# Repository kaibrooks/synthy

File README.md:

# synthy
PROJECT THEREMIZER

This file describes the THEREMIZER built by Bader Almatouq, Kai Brooks, Andrew Forsman, and Jeff Roman in Fall 
of 2019 for ECE 411 at Portland State University.

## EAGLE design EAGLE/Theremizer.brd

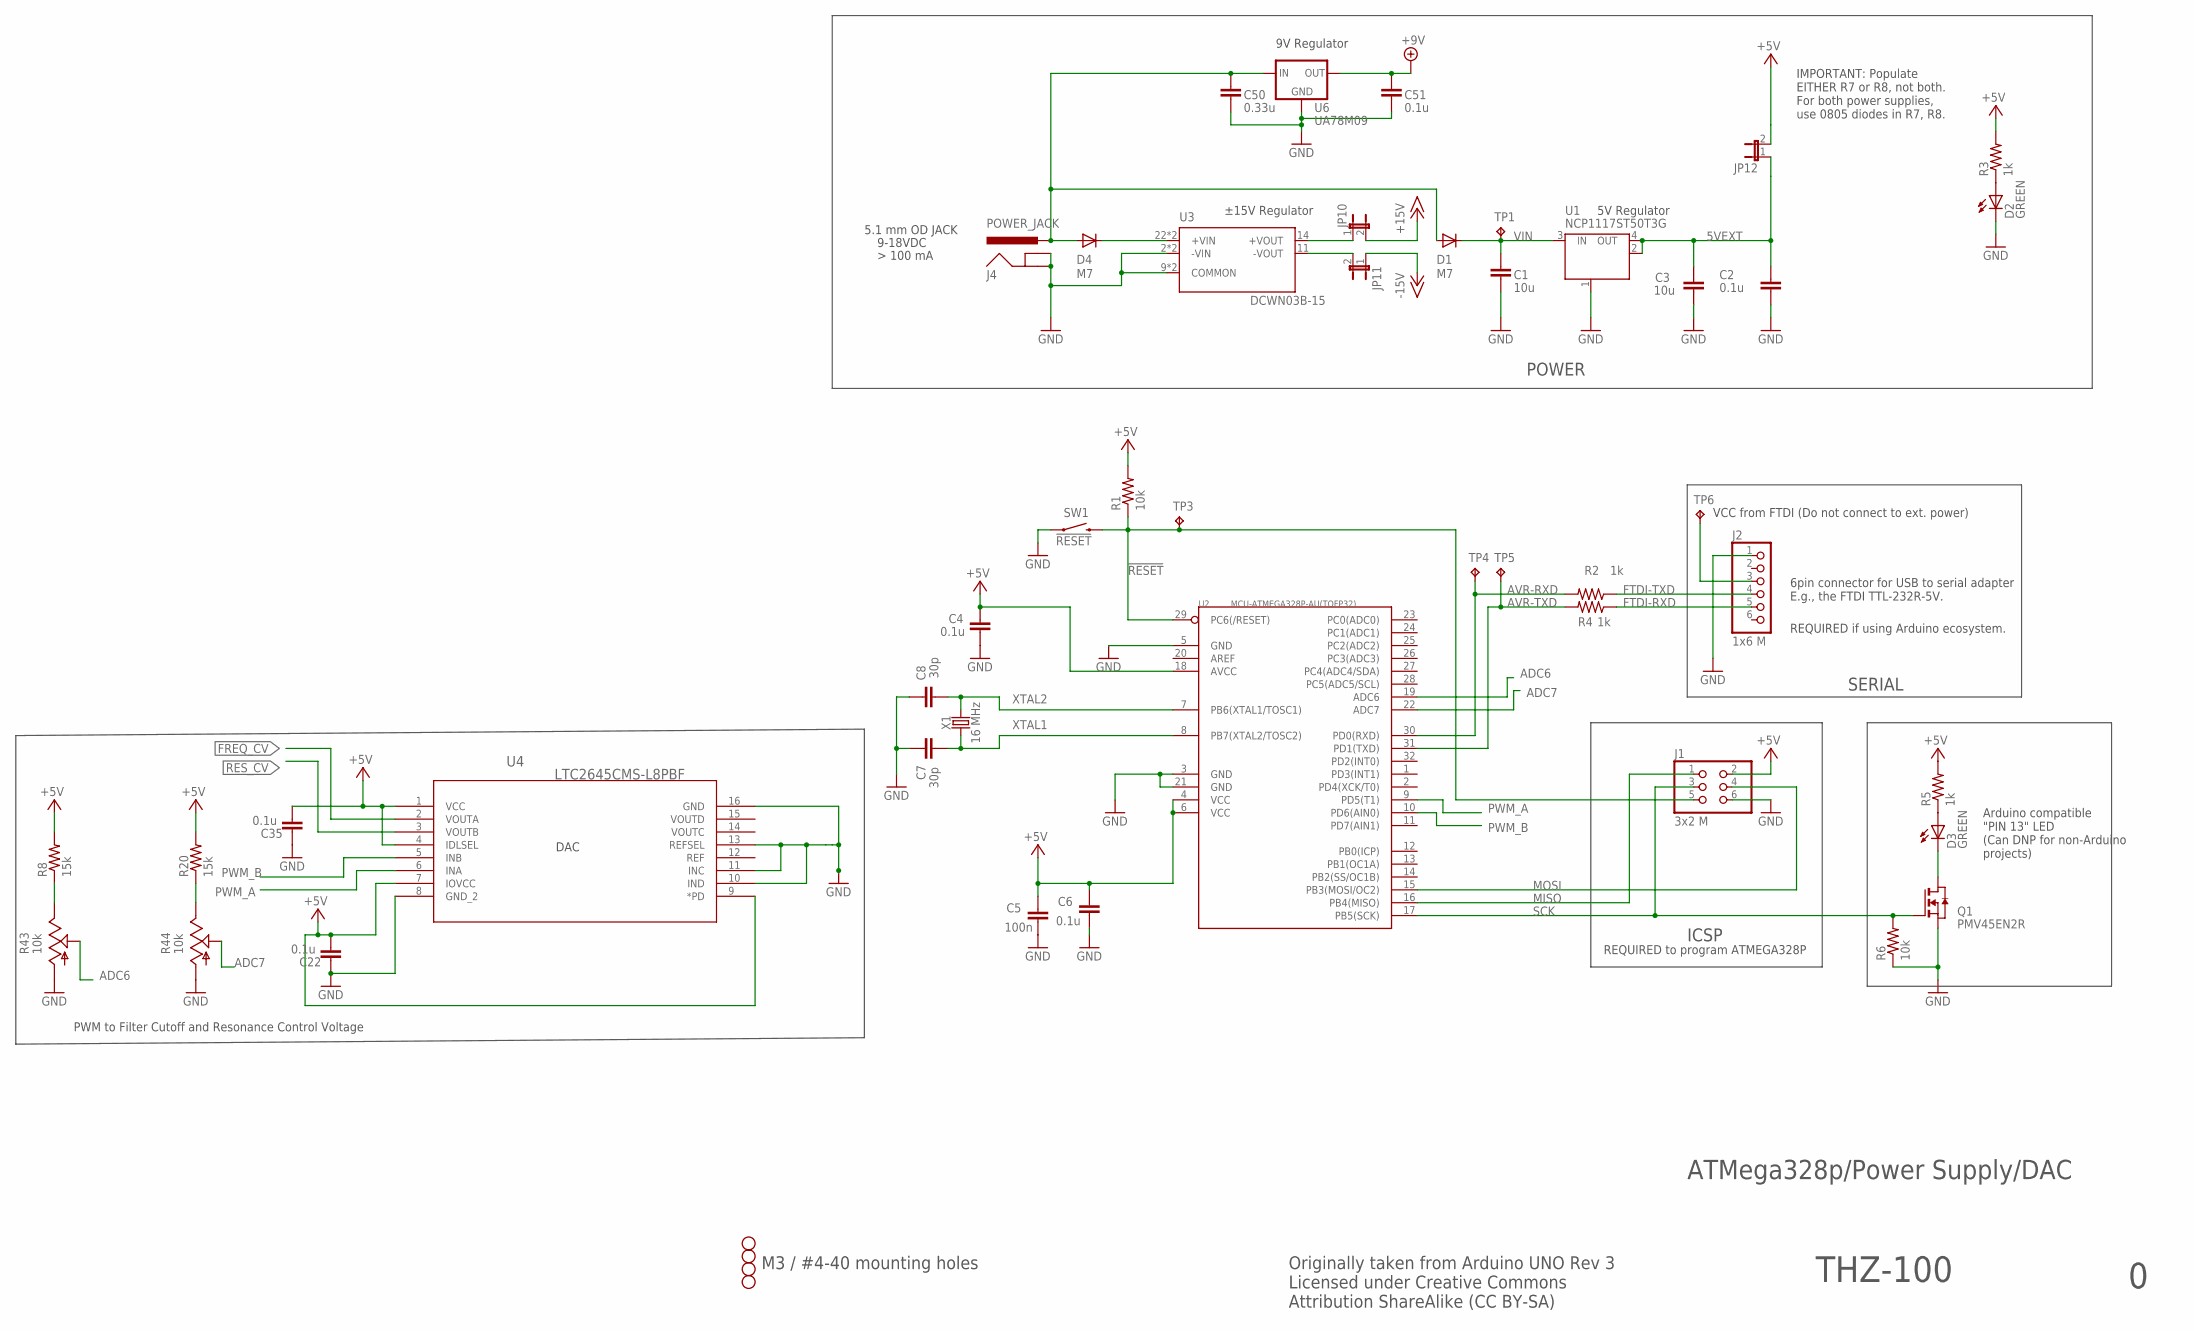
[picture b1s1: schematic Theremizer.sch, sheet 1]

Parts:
C1, C3: 10u; C0805; MPN CL21A106KOQNNNG
C2, C4, C6: 0.1u; C0805; MPN CL21B104KBCNNNC
C5: 100n; C0805; MPN CL21B104KBCNNNC
C7: 30p; C0805; MPN CL21C180JBANNNC
C8: 30p; C0805; MPN CL21C300JBANNNC
C22: 0.1u; C0805K; MPN CL21C300JBANNNC
C35: 0.1u; C0805; MPN CL21C300JBANNNC
C50: 0.33u; C0805; MPN CL21A106KOQNNNG
C51: 0.1u; C0805; MPN CL21A106KOQNNNG
D1, D4: M7; SMB; MPN 10BQ030TR
D2, D3: GREEN; CHIP-LED0805; MPN 150080GS75000
H1, H2, H3, H4: STAND-OFF
J1: 3x2 M; 2X03; MPN M20-9980345
J2: 1x6 M; 1X06; MPN PRPC006SAAN-RC
J4: POWER_JACK; POWER_JACK_PTH; MPN PJ-202A
JP10, JP11, JP12: JP1E; JP1
Q1: PMV45EN2R; SOT-23; MPN PMV45EN2R
R1, R6: 10k; R0805; MPN RC0805FR-0710KL
R2, R3, R4, R5: 1k; R0805; MPN RC0805FR-071KL
R8, R20: 15k; R0805; MPN RC0805FR-0710KL
R43, R44: 10k; ECP10P
SW1: !RESET; TACTILE_SWITCH_SMD; MPN RS-187R05A2-DS MT RT
TP1, TP3, TP4, TP5, TP6: TPPAD1-13; P1-13
U1: NCP1117ST50T3G; SOT223; MPN NCP1117ST50T3G
U2: MCU-ATMEGA328P-AU(TQFP32); TQFP32-0.8-7X7MM
U3: DCWN03B-15; DIP1549W45P254L3404H940Q24
U4: LTC2645CMS-L8PBF; MSOP-16_MS
U6: UA78M09; DPACK
X1: 16 MHz; HC49UP; MPN ECS-160-18-5PX-TR

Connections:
5VEXT: C2.2, C3.1, JP12.1, U1.2 (OUT), U1.4 (OUT)
!RESET: J1.5, R1.1, SW1.3 (2), TP3.TP, U2.29 (PC6(/RESET))
+5V: C4.2, C5.2, C6.2, C22.1, C35.1, J1.2, JP12.2, R1.2, R3.2, R5.2, R8.2, R20.2, U2.4 (VCC), U2.6 (VCC), U2.18 (AVCC), U4.1 (VCC), U4.4 (IDLSEL), U4.7 (IOVCC), U4.9 (*PD); also elsewhere on the board
+9V: C51.1, U6.3 (OUT); also elsewhere on the board
+15V: JP10.2; also elsewhere on the board
-15V: JP11.1; also elsewhere on the board
ADC6: R43.S, U2.19 (ADC6)
ADC7: R44.S, U2.22 (ADC7)
AVR-RXD: R2.2, TP4.TP, U2.30 (PD0(RXD))
AVR-TXD: R4.2, TP5.TP, U2.31 (PD1(TXD))
FREQ_CV: U4.2 (VOUTA); also elsewhere on the board
FTDI-RXD: J2.5, R4.1
FTDI-TXD: J2.4, R2.1
GND: C1.2, C2.1, C3.2, C4.1, C5.1, C6.1, C7.2, C8.2, C22.2, C35.2, C50.2, C51.2, D2.C, J1.6, J2.1, J4.GND, J4.GNDBREAK, Q1.2 (S), R6.1, R43.A, R44.A, SW1.1, U1.1 (GND/ADJ), U2.3 (GND), U2.5 (GND), U2.21 (GND), U3.2 (-VIN), U3.3 (-VIN), U3.9 (COMMON), U3.16 (COMMON), U4.8 (GND_2), U4.10 (IND), U4.11 (INC), U4.13 (REFSEL), U4.16 (GND), U6.4 (GND); also elsewhere on the board
MISO: J1.1, U2.16 (PB4(MISO))
MOSI: J1.4, U2.15 (PB3(MOSI/OC2))
unnamed: D3.A, R5.1
unnamed: D2.A, R3.1
unnamed: D3.C, Q1.1 (D)
unnamed: J2.3, TP6.TP
unnamed: D4.C, U3.22 (+VIN), U3.23 (+VIN)
unnamed: JP10.1, U3.14 (+VOUT)
unnamed: JP11.2, U3.11 (-VOUT)
unnamed: R8.1, R43.E
unnamed: R20.1, R44.E
PWM_A: U2.9 (PD5(T1)), U4.6 (INA)
PWM_B: U2.10 (PD6(AIN0)), U4.5 (INB)
RES_CV: U4.3 (VOUTB); also elsewhere on the board
SCK: J1.3, Q1.3 (G), R6.2, U2.17 (PB5(SCK))
VIN: C1.1, D1.C, TP1.TP, U1.3 (IN)
XTAL1: C7.1, U2.8 (PB7(XTAL2/TOSC2)), X1.1
XTAL2: C8.1, U2.7 (PB6(XTAL1/TOSC1)), X1.2

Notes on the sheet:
9-18VDC
POWER
ICSP
5.1 mm OD JACK
6pin connector for USB to serial adapter E.g., the FTDI TTL-232R-5V.
REQUIRED if using Arduino ecosystem.
M3 / #4-40 mounting holes
SERIAL
REQUIRED to program ATMEGA328P
Arduino compatible "PIN 13" LED (Can DNP for non-Arduino projects)
VCC from FTDI (Do not connect to ext. power)
IMPORTANT: Populate EITHER R7 or R8, not both. For both power supplies, use 0805 diodes in R7, R8.
Originally taken from Arduino UNO Rev 3 Licensed under Creative Commons Attribution ShareAlike (CC BY-SA)
PWM to Filter Cutoff and Resonance Control Voltage
DAC
ATMega328p/Power Supply/DAC
9V Regulator
±15V Regulator
5V Regulator
THZ-100

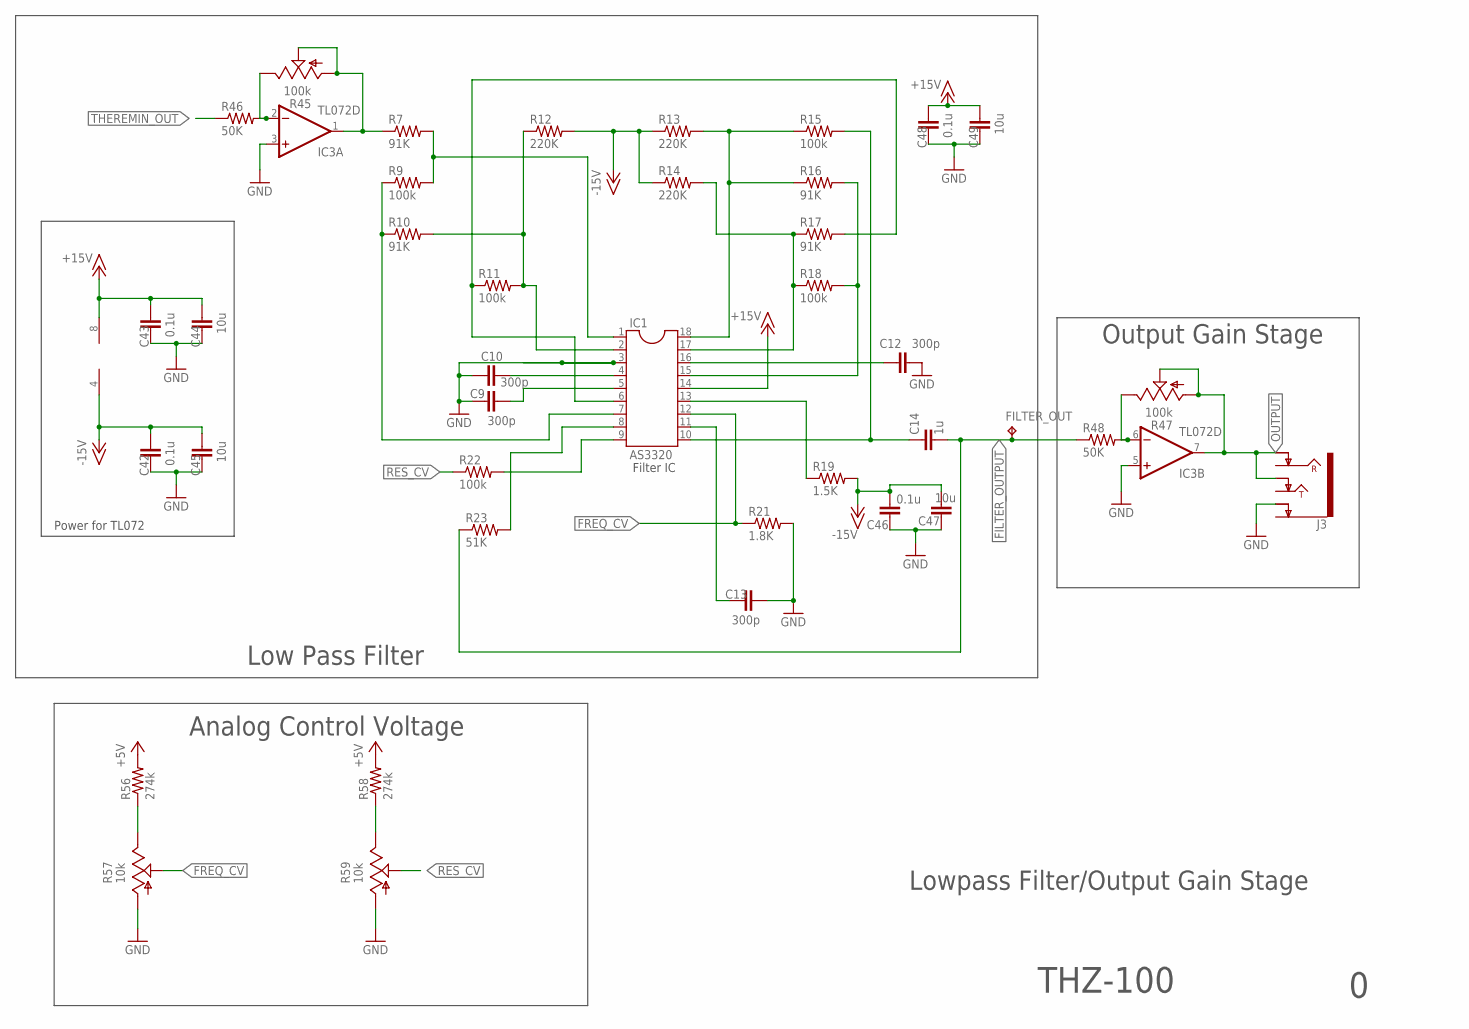
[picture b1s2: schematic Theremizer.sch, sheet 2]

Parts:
C9, C10, C12, C13: 300p; C0805
C14: 1u; C0805
C42, C43, C46, C48: 0.1u; C0805
C44, C45, C47, C49: 10u; C0805
FILTER_OUT: TPB2,54; B2,54
IC1: AS3320; SOCKET-18
IC3: TL072D; SO08
J3: AUDIO_JACK_TRS_0.25"_PTH_RA; AUDIO_JACK_0.25"_TRS_PTH_RA
R7, R10, R16, R17: 91K; R0805
R9, R11, R15, R18, R22: 100k; R0805
R12, R13, R14: 220K; R0805
R19: 1.5K; R0805
R21: 1.8K; R0805
R23: 51K; R0805
R45, R47: 100k; ECP10P
R46, R48: 50K; R0805
R56, R58: 274k; R0805
R57, R59: 10k; ECP10P

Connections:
+5V: R56.2, R58.2; also elsewhere on the board
+15V: C43.2, C44.2, C48.2, C49.2, IC1.14, IC3.8 (V+); also elsewhere on the board
-15V: C42.2, C45.2, C46.2, C47.2, IC3.4 (V-), R12.2, R13.1, R14.1, R19.2; also elsewhere on the board
FILTER_OUTPUT: C14.2, FILTER_OUT.TP, R23.1, R48.1; also elsewhere on the board
FREQ_CV: IC1.12, R21.1, R57.S; also elsewhere on the board
GND: C9.1, C10.1, C12.2, C13.2, C42.1, C43.1, C44.1, C45.1, C46.1, C47.1, C48.1, C49.1, IC1.3, IC3.3 (+IN), IC3.5 (+IN), J3.SLEEVE-NORM (EARTH-NORM), R21.2, R57.A, R59.A; also elsewhere on the board
unnamed: IC1.1, R7.2, R9.2
unnamed: IC1.7, R9.1, R10.1
unnamed: C9.2, IC1.5
unnamed: C10.2, IC1.4
unnamed: IC1.2, R10.2, R11.2, R12.1
unnamed: IC1.6, R11.1, R17.2
unnamed: C14.1, IC1.10, R15.2
unnamed: IC1.18, R13.2, R15.1, R16.1
unnamed: IC1.17, R14.2, R17.1, R18.1
unnamed: IC1.15, R16.2, R18.2
unnamed: C12.1, IC1.16
unnamed: IC1.13, R19.1
unnamed: C13.1, IC1.11
unnamed: IC3.2 (-IN), R45.E, R46.2
unnamed: IC1.8, R23.2
unnamed: IC1.9, R22.2
unnamed: R56.1, R57.E
unnamed: IC3.1 (OUT), R7.1, R45.A, R45.S
unnamed: IC3.6 (-IN), R47.E, R48.2
unnamed: R58.1, R59.E
OUTPUT: IC3.7 (OUT), J3.RING-NORM, J3.TIP-NORM, R47.A, R47.S; also elsewhere on the board
RES_CV: R22.1, R59.S; also elsewhere on the board
THEREMIN_OUT: R46.1; also elsewhere on the board

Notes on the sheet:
Low Pass Filter
Power for TL072
Output Gain Stage
Filter IC
Analog Control Voltage
Lowpass Filter/Output Gain Stage
THZ-100

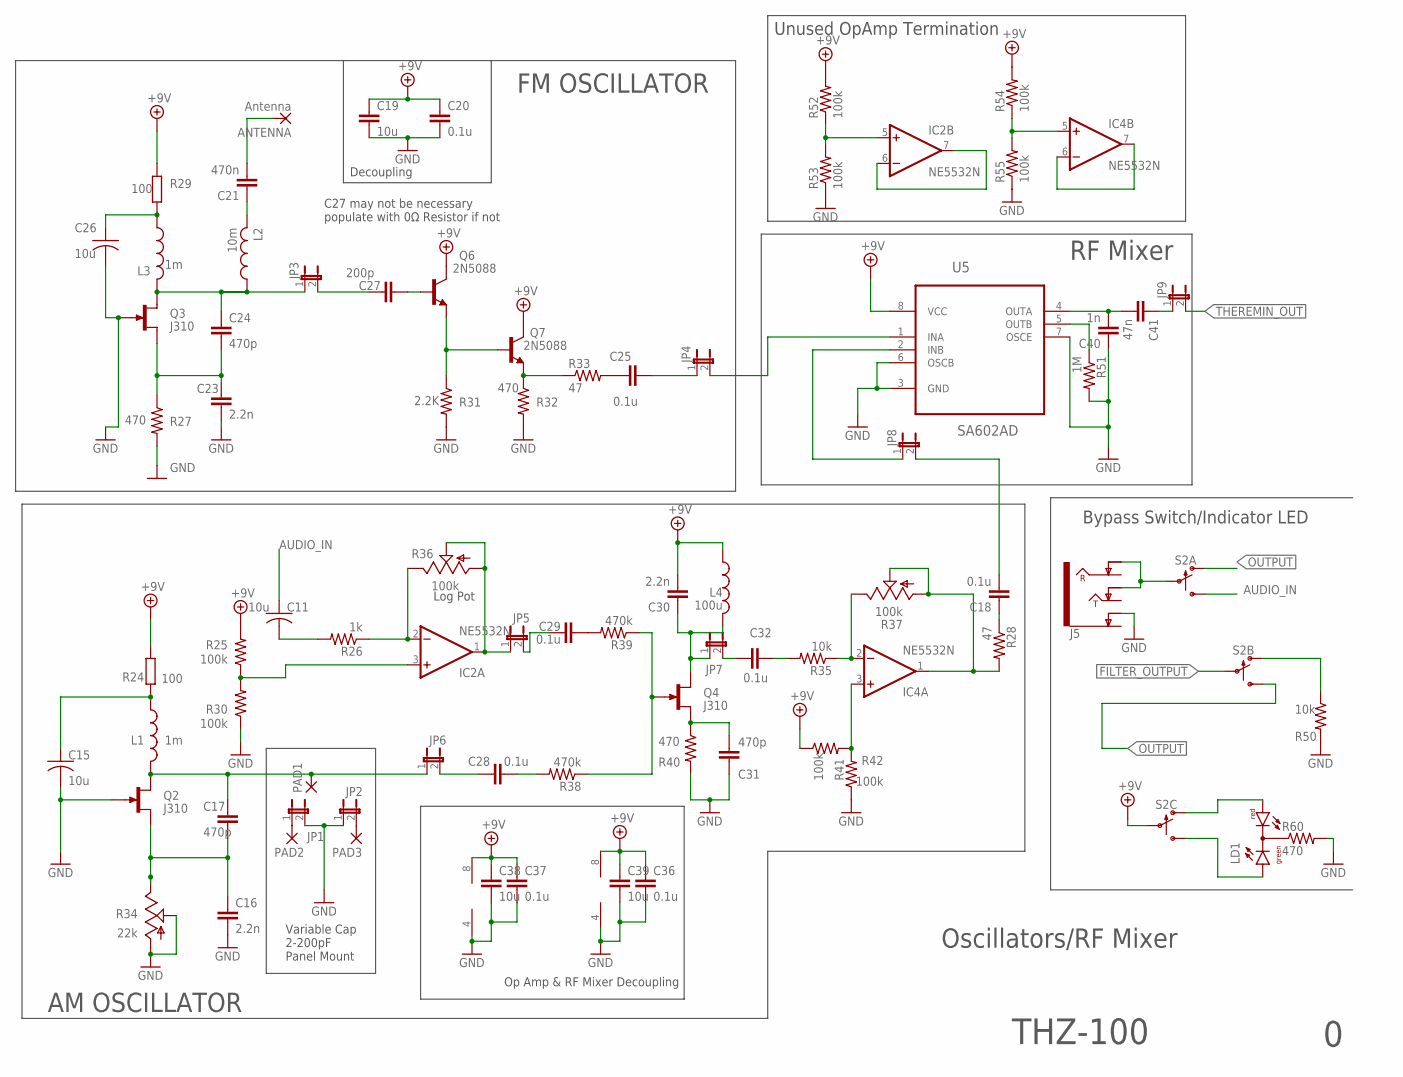
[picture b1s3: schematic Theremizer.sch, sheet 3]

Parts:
ANTENNA: Antenna; 2,54/1,1
C11, C15, C26: 10u; C050-025X075
C16, C23, C30: 2.2n; C0805
C17, C24, C31: 470p; C0805
C18, C20, C25, C28, C29, C32, C36, C37: 0.1u; C0805
C19, C38, C39: 10u; C0805
C21: 470n; C0805
C27: 200p; C0805
C40: 1n; C0805
C41: 47n; C0805
IC2, IC4: NE5532N; DIL08
J5: AUDIO_JACK_TRS_0.25"_PTH_RA; AUDIO_JACK_0.25"_TRS_PTH_RA
JP1, JP2, JP3, JP4, JP5, JP6, JP7, JP8, JP9: JP1E; JP1
L1, L3: 1m; 6000-XXXX-RC
L2: 10m; 6000-XXXX-RC
L4: 100u; 6000-XXXX-RC
LD1: DUOLED-RG-C; DUOLED-C-5MM
PAD1, PAD2, PAD3: 2,15/1,0
Q2, Q3, Q4: J310; TO92R
Q6, Q7: 2N5088; TO92
R24, R29: 100; PRL1632
R25, R30, R41, R42, R52, R53, R54, R55: 100k; R0805
R26: 1k; R0805
R27, R32, R40, R60: 470; R0805
R28, R33: 47; R0805
R31: 2.2K; R0805
R34: 22k; B64Y
R35, R50: 10k; R0805
R36, R37: 100k; ECP10P
R38, R39: 470k; R0805
R51: 1M; R0805
S2: SWITCH-3PDT-PTH-STOMP; STOMP_SWITCH_3PDT
U5: SA602AD; SO8

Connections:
+9V: C19.1, C20.1, C30.2, C36.1, C37.1, C38.1, C39.1, IC2.8 (V+), IC4.8 (V+), L4.1, Q6.1 (C), Q7.1 (C), R24.2, R25.2, R29.1, R41.1, R52.2, R54.2, S2.P$8, U5.8 (VCC); also elsewhere on the board
ANTENNA: ANTENNA.1, C21.2
AUDIO_IN: C11.1, S2.P$3 (S)
FILTER_OUTPUT: S2.P$5; also elsewhere on the board
GND: C15.2, C16.2, C19.2, C20.2, C23.2, C26.2, C31.1, C36.2, C37.2, C38.2, C39.2, C40.1, IC2.4 (V-), IC4.4 (V-), J5.SLEEVE-NORM (EARTH-NORM), JP1.2, JP2.1, Q2.G, Q3.G, R27.2, R30.1, R31.2, R32.2, R34.A, R34.S, R40.2, R42.1, R50.2, R51.2, R53.1, R55.1, R60.2, U5.3 (GND), U5.6 (OSCB), U5.7 (OSCE); also elsewhere on the board
unnamed: C21.1, L2.2
unnamed: C15.1, L1.1, R24.1
unnamed: C18.1, R28.1
unnamed: JP4.2, U5.1 (INA)
unnamed: C25.1, R33.2
unnamed: C24.1, JP3.1, L2.1, L3.2, Q3.D
unnamed: C27.2, Q6.2 (B)
unnamed: IC2.3 (+IN), R25.1, R30.2
unnamed: IC4.3 (+IN), R41.2, R42.2
unnamed: Q6.3 (E), Q7.2 (B), R31.1
unnamed: Q7.3 (E), R32.1, R33.1
unnamed: C32.1, R35.2
unnamed: C16.1, C17.2, Q2.S, R34.E
unnamed: C17.1, JP6.1, L1.2, PAD1.1, Q2.D
unnamed: JP8.1, U5.2 (INB)
unnamed: J5.RING-NORM, J5.TIP-NORM, S2.P$2
unnamed: R50.1, S2.P$4 (O)
unnamed: C11.2, R26.2
unnamed: IC2.2 (-IN), R26.1, R36.E
unnamed: IC2.1 (OUT), JP5.1, R36.A, R36.S
unnamed: C29.2, R39.2
unnamed: C28.2, R38.2
unnamed: Q4.G, R38.1, R39.1
unnamed: C30.1, JP7.1, L4.2, Q4.D
unnamed: C31.2, Q4.S, R40.1
unnamed: IC4.2 (-IN), R35.1, R37.E
unnamed: IC4.1 (OUT), R28.2, R37.A, R37.S
unnamed: LD1.AR, S2.P$7 (O)
unnamed: C26.1, L3.1, R29.2
unnamed: LD1.AX (AG), S2.P$9 (S)
unnamed: R51.1, U5.5 (OUTB)
unnamed: IC2.6 (-IN), IC2.7 (OUT)
unnamed: IC2.5 (+IN), R52.1, R53.2
unnamed: IC4.5 (+IN), R54.1, R55.2
unnamed: IC4.6 (-IN), IC4.7 (OUT)
unnamed: C23.1, C24.2, Q3.S, R27.1
unnamed: JP1.1, PAD2.1
unnamed: JP2.2, PAD3.1
unnamed: C27.1, JP3.2
unnamed: C25.2, JP4.1
unnamed: C29.1, JP5.2
unnamed: C28.1, JP6.2
unnamed: C32.2, JP7.2
unnamed: C18.2, JP8.2
unnamed: C40.2, C41.2, U5.4 (OUTA)
unnamed: LD1.C, R60.1
unnamed: C41.1, JP9.1
OUTPUT: S2.P$1 (O), S2.P$6 (S); also elsewhere on the board
THEREMIN_OUT: JP9.2; also elsewhere on the board

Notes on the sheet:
AM OSCILLATOR
FM OSCILLATOR
C27 may not be necessary populate with 0Ω Resistor if not
Decoupling
Op Amp & RF Mixer Decoupling
RF Mixer
Bypass Switch/Indicator LED
Log Pot
Unused OpAmp Termination
Variable Cap 2-200pF Panel Mount
Oscillators/RF Mixer
THZ-100

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
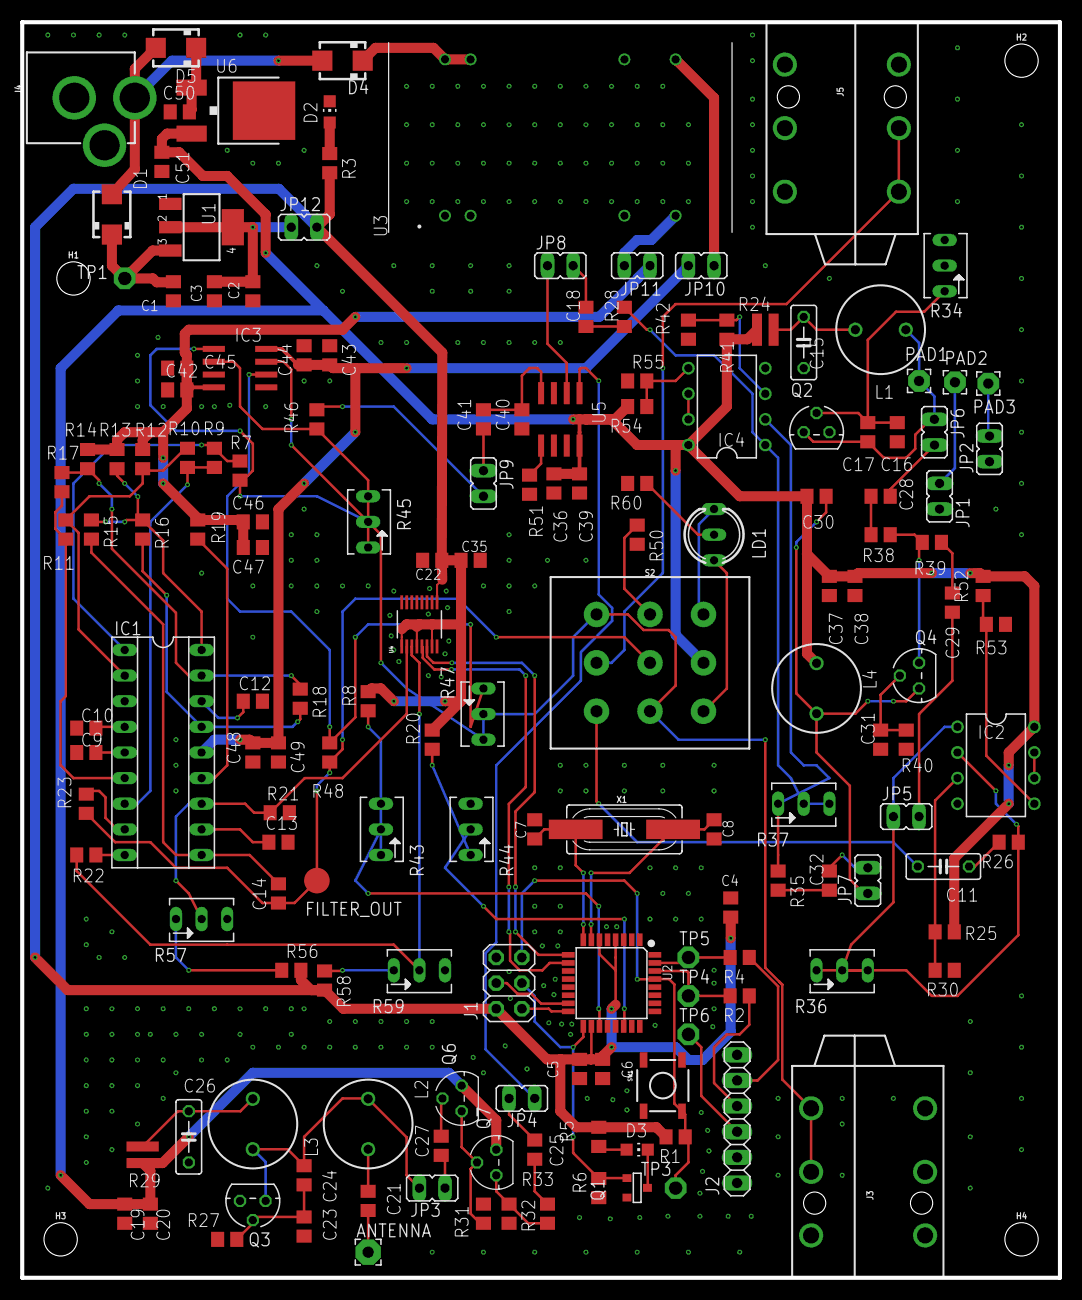
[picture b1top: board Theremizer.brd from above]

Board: 2 copper layers, 102.9 x 124.5 mm, 168 parts (0 on the bottom side), 106 nets.

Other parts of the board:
D5: M7; SMA

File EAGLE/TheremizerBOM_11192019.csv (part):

"Qty","Value","Device","Package","Parts","Description","AVAILABILITY","DESC","DESCRIPTION","DIGI-KEY_PART_NUMBER","DIGI-KEY_PURCHASE_URL","MF","MFR","MP","MPN","OC_FARNELL","OC_NEWARK","PACKAGE","POPULARITY","PRICE","PROD_ID","SF_ID","SPICEPREFIX","TP_SIGNAL_NAME",
"3","","2,15/1,0","2,15/1,0","PAD1, PAD2, PAD3","THROUGH-HOLE PAD","","","","","","","","","","","","","11","","","","","",
"1","","DUOLED-RG-C","DUOLED-C-5MM","LD1","DUO LED","","","","","","","","","","","","","1","","","","","",
"9","","JP1E","JP1","JP1, JP2, JP3, JP4, JP5, JP6, JP7, JP8, JP9","JUMPER","","","","","","","","","","","","","61","","","","","",
"1","!RESET","SWITCH-MOMENTARY-2SMD","TACTILE_SWITCH_SMD","SW1","Various NO switches- pushbuttons, reed, etc","","SWITCH TACTILE SPST-NO 0.05A 12V","","","","","C&K","","RS-187R05A2-DS MT RT","","","","","","","","","",
"3","0","R-US_R0805","R0805","R8, R20, R49","RESISTOR, American symbol","","","","","","","Yageo","","RC0805JR-070RL","","","","85","","","","R","",
"11","0.1u","C-EUC0805","C0805","C18, C20, C25, C28, C29, C36, C37, C42, C43, C46, C48","CAPACITOR, European symbol","","","","","","","","","","","","","88","","","","C","",
"1","0.1u","C-EUC0805","C0805","C51","CAPACITOR, European symbol","","","","","","","Samsung","","CL21A106KOQNNNG","","","","88","","","","C","",
"3","0.1u","C-EUC0805","C0805","C2, C4, C6","CAPACITOR, European symbol","","","","","","","Samsung","","CL21B104KBCNNNC","","","","88","","","","C","",
"1","0.1u","C-EUC0805","C0805","C35","CAPACITOR, European symbol","","CAP CER 30PF 50V C0G/NP0 0805","","","","","Samsung","","CL21C300JBANNNC","","","","88","","","","C","",
"1","0.1u","C-EUC0805K","C0805K","C22","CAPACITOR, European symbol","","CAP CER 30PF 50V C0G/NP0 0805","","","","","Samsung","","CL21C300JBANNNC","","","","52","","","","C","",
"1","0.33u","C-EUC0805","C0805","C50","CAPACITOR, European symbol","","","","","","","Samsung","","CL21A106KOQNNNG","","","","88","","","","C","",
"1","1.5K","R-US_R0805","R0805","R19","RESISTOR, American symbol","","","","","","","","","","","","","85","","","","R","",
"1","1.8K","R-US_R0805","R0805","R21","RESISTOR, American symbol","","","","","","","","","","","","","85","","","","R","",
"2","100","R-EU_PRL1632","PRL1632","R24, R29","RESISTOR, European symbol","","","","","","","","","","","","","0","","","","R","",
"13","100k","R-US_R0805","R0805","R9, R11, R15, R18, R22, R25, R30, R41, R42, R52, R53, R54, R55","RESISTOR, American symbol","","","","","","","","","","","","","85","","","","R","",
"4","100k","TRIM_US-ECP10P","ECP10P","R36, R37, R45, R47","POTENTIOMETER","","","","","","","","","","","","","0","","","","","",
"1","100n","C-EUC0805","C0805","C5","CAPACITOR, European symbol","","","","","","","Samsung","","CL21B104KBCNNNC","","","","88","","","","C","",
"1","100u","L-US6000-XXX-RC","6000-XXXX-RC","L4","INDUCTOR, American symbol","","","","","","","","","","","","","5","","","","L","",
"2","10k","R-US_R0805","R0805","R35, R50","RESISTOR, American symbol","","","","","","","","","","","","","85","","","","R","",
"2","10k","R-US_R0805","R0805","R1, R6","RESISTOR, American symbol","","","","","","","Yageo","","RC0805FR-0710KL","","","","85","","","","R","",
"4","10k","TRIM_US-ECP10P","ECP10P","R43, R44, R57, R59","POTENTIOMETER","","","","","","","","","","","","","0","","","","","",
"1","10m","L-US6000-XXX-RC","6000-XXXX-RC","L2","INDUCTOR, American symbol","","","","","","","","","","","","","5","","","","L","",
"8","10u","C-EUC0805","C0805","C19, C32, C38, C39, C44, C45, C47, C49","CAPACITOR, European symbol","","","","","","","","","","","","","88","","","","C","",
"2","10u","C-EUC0805","C0805","C1, C3","CAPACITOR, European symbol","","","","","","","Samsung","","CL21A106KOQNNNG","","","","88","","","","C","",
"3","10u","C-US050-025X075","C050-025X075","C11, C15, C26","CAPACITOR, American symbol","","","","","","","","","","","","","0","","","","C","",
"1","16 MHz","CRYSTALSMD-HC49UP","HC49UP","X1","Crystals (Generic)","","CRYSTAL 16.000 MHZ 18PF SMD","","","","","ECS","","ECS-160-18-5PX-TR","","","","","","","","","",
"1","1M","R-US_R0805","R0805","R51","RESISTOR, American symbol","","","","","","","","","","","","","85","","","","R","",
"1","1k","R-US_R0805","R0805","R26","RESISTOR, American symbol","","","","","","","","","","","","","85","","","","R","",
"4","1k","R-US_R0805","R0805","R2, R3, R4, R5","RESISTOR, American symbol","","","","","","","Yageo","","RC0805FR-071KL","","","","85","","","","R","",
"2","1m","L-US6000-XXX-RC","6000-XXXX-RC","L1, L3","INDUCTOR, American symbol","","","","","","","","","","","","","5","","","","L","",
"1","1n","C-EUC0805","C0805","C40","CAPACITOR, European symbol","","","","","","","","","","","","","88","","","","C","",
"1","1u","C-EUC0805","C0805","C14","CAPACITOR, European symbol","","","","","","","","","","","","","88","","","","C","",
"1","1x6 M","PINHD-1X6","1X06","J2","PIN HEADER","","","","","","","Sullins","","PRPC006SAAN-RC","","","","","","","","","",
"1","2.2K","R-US_R0805","R0805","R31","RESISTOR, American symbol","","","","","","","","","","","","","85","","","","R","",
"3","2.2n","C-EUC0805","C0805","C16, C23, C30","CAPACITOR, European symbol","","","","","","","","","","","","","88","","","","C","",
"1","200p","C-EUC0805","C0805","C27","CAPACITOR, European symbol","","","","","","","","","","","","","88","","","","C","",
"3","220K","R-US_R0805","R0805","R12, R13, R14","RESISTOR, American symbol","","","","","","","","","","","","","85","","","","R","",
"1","22k","TRIM_US-PT10","PT-10","R34","POTENTIOMETER","","","","","","","","","","","","","0","","","","","",
"2","274k","R-US_R0805","R0805","R56, R58","RESISTOR, American symbol","","","","","","","","","","","","","85","","","","R","",
"2","2N5088","2N5088","TO92","Q6, Q7","NPN Transistor","","","","","","","","","","","","","0","","","","","",
"4","300p","C-EUC0805","C0805","C9, C10, C12, C13","CAPACITOR, European symbol","","","","","","","","","","","","","88","","","","C","",
"1","30p","C-EUC0805","C0805","C7","CAPACITOR, European symbol","","CAP CER 30PF 50V C0G/NP0 0805","","","","","Samsung","","CL21C180JBANNNC","","","","88","","","","C","",
"1","30p","C-EUC0805","C0805","C8","CAPACITOR, European symbol","","CAP CER 30PF 50V C0G/NP0 0805","","","","","Samsung","","CL21C300JBANNNC","","","","88","","","","C","",
"1","3x2 M","PINHD-2X3","2X03","J1","PIN HEADER","","","","","","","Harwin","","M20-9980345","","","","","","","","","",
"2","47","R-US_R0805","R0805","R28, R33","RESISTOR, American symbol","","","","","","","","","","","","","85","","","","R","",
"4","470","R-US_R0805","R0805","R27, R32, R40, R60","RESISTOR, American symbol","","","","","","","","","","","","","85","","","","R","",
"2","470k","R-US_R0805","R0805","R38, R39","RESISTOR, American symbol","","","","","","","","","","","","","85","","","","R","",
"1","470n","C-EUC0805","C0805","C21","CAPACITOR, European symbol","","","","","","","","","","","","","88","","","","C","",
"3","470p","C-EUC0805","C0805","C17, C24, C31","CAPACITOR, European symbol","","","","","","","","","","","","","88","","","","C","",
"1","47n","C-EUC0805","C0805","C41","CAPACITOR, European symbol","","","","","","","","","","","","","88","","","","C","",
"2","50K","R-US_R0805","R0805","R46, R48","RESISTOR, American symbol","","","","","","","","","","","","","85","","","","R","",
"1","51K","R-US_R0805","R0805","R23","RESISTOR, American symbol","","","","","","","","","","","","","85","","","","R","",
"4","91K","R-US_R0805","R0805","R7, R10, R16, R17","RESISTOR, American symbol","","","","","","","","","","","","","85","","","","R","",
"1","AS3320","DIL18S","SOCKET-18","IC1","Dual In Line / Socket","","","","","","","","","","","","","0","","","","","",
"2","AUDIO_JACK_TRS_0.25"_PTH_RA","AUDIO_JACK_TRS_0.25"_PTH_RA","AUDIO_JACK_0.25"_TRS_PTH_RA","J3, J5","Audio Jack, 1/4" TRS jack, horizontal, PTH, aka "Phono jack"","","","","","","","","","","","","","","","CONN-12339","COM-11144","","",
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
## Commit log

2019-10-12 Testing...testing.
2019-10-14 Basic Oscillator Schematics with Antenna Loading Coil and tuning circuit
2019-10-15 Added AM modulator circuit, good antenna coil, 50ohm buffers to both oscillators.
2019-10-16 Homework 2 - 3 Ideas
2019-10-16 Didn't have word wrap on 😑
2019-10-16 Homework 2 - 3 Ideas
    .rtf wasn't displaying correctly
2019-10-16 Added Kai's bad idea
2019-10-16 My idea plus adds to schematic
2019-10-16 Added details
2019-10-16 Update Homework2_3_Ideas.txt
    fixed spacing.
2019-10-16 Finalized HW2
2019-10-16 HW2 Final
    haha, this one is final haha haha 😅
2019-10-17 BOM Initial
    I will add more to this as the schematic is populated
2019-10-17 More components
2019-10-21 BOM Update
2019-10-21 Auto stash before merge of "master" and "origin/master"
2019-10-23 High level block diagram of product
2019-10-23 PDS Stuff
2019-10-23 Added Optional Audio In to BD
    Also, added original schematic file for further edits if needed.
2019-10-23 More PDS
2019-10-23 PDS Mostly Done
2019-10-24 More More PDS
2019-10-24 Adjusted language and format
2019-10-24 Cut it down to 3 pages because I can't read requirements
2019-10-24 Added version because I can't read requirements
2019-10-24 Added stuff to block diagram and slight change to header
2019-10-24 Needs and Objective statements added
2019-10-24 More
2019-10-29 Changed oscillators to common base JFET, set up 50ohm output buffers.
2019-10-30 Schematic, probably 40% Done
2019-10-30 Added filter and theremin/freq mixer to circuit
2019-10-31 Breadboard things
2019-11-04 Finished front end, oscillators and input circuit through to mixer. 100mV-1V inputs.
2019-11-06 Initial Board
2019-11-06 Added project headers
2019-11-06 Minor update
2019-11-06 Project file for Theremizer and examples
2019-11-07 Added test and documentation branches. Still needs personnel assignments.
2019-11-07 Assigned personnel assignments and added final documentation
2019-11-07 caught a schematic error in the tuning nodes on the oscillators
2019-11-07 Inital board & bunch of schematic changes
2019-11-07 Updated version of project
2019-11-07 More project
2019-11-07 Project garbage
2019-11-07 Added test points
2019-11-07 Initial BOM commit
2019-11-07 Minor changes/ERC
2019-11-07 Package size change
2019-11-13 Added existing project sections from Asana
2019-11-14 Functional Decomposition of Theremizer
    Contains the PDF of the High level BD, Next level BD, and individual module top level BD's for the project.
2019-11-14 BOM Update, more to come before 10AM
2019-11-14 Almost complete BOM
2019-11-14 Test point for filter out
2019-11-15 Added bypass, new mixer
2019-11-15 Added stuff
2019-11-16 Changed cap values for mixer output, added decoupling caps, 9V regulator
2019-11-18 Fixed AM modulator and finalized value choices
2019-11-18 most of BOM stuff
2019-11-18 finalized spice scheme, digikey bom, total bom
2019-11-19 Added decoupling caps and analog CV
2019-11-19 updated to reflect currently purchased items
2019-11-19 Our Design Review Results
2019-11-20 Last BOM
2019-11-20 Redid layout, hopefully better
2019-11-20 Board laid out by hand, still needs vias
2019-11-20 Now with 1000000x more vias
2019-11-21 Auto stash before merge of "master" and "origin/master"
    Hopefully complete BOM and list of all used materials/sources
2019-11-21 Final Schematic/Board Layout
2019-11-21 added .eps for logo
2019-11-22 Added start of HTTP get / post UML information
2019-11-22 Added HTTP GET / POST / PUT / whatever document
2019-11-22 Final Digikey BOM
2019-11-22 Final Digikey BOM/final Eagle BOM with values matching actual components
2019-11-25 Beginnings of test documentation file
2019-11-27 Added assumptions
2019-11-28 Connected airwire from RES_CV nodes
2019-11-28 Potential Final Version of HW7
2019-11-28 Finalized UML HW
2019-11-30 Two Use Cases for the Test Plan HW, both Excel Source and PDF
2019-11-30 FIrst draft of test plan complete
2019-12-04 Buncha random things, added .png of logo
2019-12-05 the oscillator in question
2019-12-06 Code to have microcontroller function as a PWM
2019-12-09 Ignored temp macOS files
2019-12-10 Added files for PPT
2019-12-10 Updated PWM code to generate correct duty cycles
2019-12-10 Board Things/Routing fixes
2019-12-11 Theremizer Level 0 and 1 Block Diagrams Updated
2019-12-11 Demo Presentation Work
2019-12-11 Added/updated slides on presentation
2019-12-11 Test Stuff and PCB layout
2019-12-11 Beta for timing
2019-12-11 Organized Repo
2019-12-11 Final Bom
2019-12-11 Update name
2019-12-11 Moved PDS

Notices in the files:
parts and their libraries:
SparkFun-Hardware: Licensing: Creative Commons ShareAlike 4.0 International - https://creativecommons.org/licenses/by-sa/4.0
SparkFun-Electromechanical: Licensing: CC v3.0 Share-Alike You are welcome to use this library for commercial purposes.
